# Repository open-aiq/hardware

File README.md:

# Open AIQ hardware

PCB designs (KiCad) for the Open AIQ air-quality monitor.
Firmware lives in [open-aiq/device](https://github.com/open-aiq/device); its
[`src/board.rs`](https://github.com/open-aiq/device/blob/main/src/board.rs) is the source of truth for the GPIO map.

## Layout

| Path | Contents |
| --- | --- |
| `pcb/proto2/` | Prototype 2: carrier PCB for the ESP32-S3 devkit with sensor connectors |
| `lib/` | Our own symbols and footprints, shared by every board |
| `scripts/` | `export.sh`, which builds a board's outputs from the command line |

Each PCB folder holds the KiCad project, the schematic and assembly PDFs, and
the fabrication outputs (Gerbers and BOM) under `fab/`. Its README
covers the parts, the pin map and what to check before you build.

Still to come: an SMT board with the ESP32-S3 module on it (in progress on the
`smt` branch), a battery-powered revision, and a 3D-printed enclosure.

## Working in KiCad

Everything here is a normal KiCad 10 project, and the KiCad files are the source
of truth. Open `pcb/<board>/<board>.kicad_pro` and edit the schematic and board
as you would any other design.

- **Libraries need no setup.** Our own symbols and footprints live in
  [`lib/`](lib), and each project finds them through `${KIPRJMOD}`. A part we've
  adapted, like the ESP32-S3 module with JLCPCB-sized vias, is saved there under
  its own name, so *Update footprints from library* keeps our changes.
- **Rules live in the project.** Net classes (wider power tracks), clearances and
  via sizes are set in *Board Setup*, so DRC is ready to go. The board opens
  with zero ERC and DRC messages. If you see one, it's new.
- **Outputs come from a jobset.** Open `<board>.kicad_jobset` from the project
  window (or *File → Jobsets*) and run it. It checks ERC and DRC, then writes the
  schematic PDF, the copper PDFs, Gerbers, drill files, the BOM and the
  placement file (plus a JLCPCB BOM for the SMT board).
- **The command line runs the same jobset.** From the repo root,
  `scripts/export.sh pcb/<board>` runs it with `kicad-cli`, then adds what KiCad
  doesn't make on its own: a zipped Gerber set, a JLCPCB-format placement file,
  3D renders and a printable PDF. That PDF has the
  schematic, the copper, a drill map, the board's hand assembly guide (if it
  has one), the BOM and placement tables, and the three renders. Merging it needs
  `qpdf` or Python's `pypdf`, and the script checks for one before it starts.

Please commit your KiCad edits and the regenerated outputs together, so the PDFs
and fab files always match the design.

## Roadmap

Planned work is tracked on the [Open AIQ Roadmap](https://github.com/orgs/open-aiq/projects/1) board.

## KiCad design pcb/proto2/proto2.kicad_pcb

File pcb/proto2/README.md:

# Proto2: devkit carrier

Proto2 is the board we use to get Open AIQ off the breadboard. The OLED sits
top-left with three buttons under it, the sensors take the middle, and your
ESP32-S3 devkit plugs into two sockets on the right with its antenna past the
top edge. It's single-sided (all copper on the bottom) and everything is
through-hole, with unplated holes, so a local shop can make it, you can etch
it at home, and you can solder it by hand.

| Top | Bottom |
| --- | --- |
|  |  |

## What's on it

| Ref | Part | Wiring |
| --- | --- | --- |
| J4, J5 | ESP32-S3-DevKitC-1, or a pin-compatible clone, on two 1×22 sockets 25.4 mm (1.0 in) apart: J4 takes devkit pins 1–22, J5 pins 23–44. The schematic shows the devkit itself as U1 | All signals are on the left header (J4). USB faces the bottom edge |
| J1 | PMS5003 particulate sensor, through its 4-wire cable, on a 1×4 socket | `TX RX VCC GND` from left to right, the cable's order, printed on the board. TX and RX are the sensor's, so TX goes to GPIO 17 (ESP RX) and RX to GPIO 18 (ESP TX). 5 V. SET and RESET aren't wired |
| J2 | 1.3 in SH1106 128×64 I2C OLED module, 4-pin socket | I2C, `GND VCC SCL SDA` from left to right, the order printed on the module's front. The module lies flat over the OLED box |
| J3, J6 | SHT30 breakout with 6 pins, on a 1×4 socket (J3) and a 1×2 socket (J6) 10.16 mm apart | I2C on J3, `SDA SCL GND VIN` from left to right on the silkscreen. J6 holds the 2 pins on the far edge, opposite SCL and SDA, for support only |
| SW1, SW2, SW3 | Right, left and pair buttons, 6 × 6 mm 4-leg tactile switches | GPIO 15, GPIO 6 and GPIO 7, active-low |
| R1, R2 | 4.7 kΩ I2C pull-ups | SDA (GPIO 5), SCL (GPIO 4) to 3.3 V, under the OLED module |
| C1–C4 | Bulk and decoupling capacitors | 47 µF + 100 nF on 5 V (C1, C2) and 10 µF + 100 nF on 3.3 V (C3, C4). All four lie flat under the devkit, in the middle of the space between its sockets |

The pins match [`src/board.rs`](https://github.com/open-aiq/device/blob/main/src/board.rs)
in open-aiq/device. Rev B moved several pins so every trace fits on one side of
the board, so flash firmware with the matching `board.rs` before you plug a
devkit in. Older breadboard builds used the previous map (SDA 8, SCL 9, buttons
4 and 5), which you'll find in the firmware README. A few pins are worth knowing
about:

- **SW3 Pair (GPIO 7)** starts BLE pairing with the phone app when you hold it
  for 3 s. Holding left and right together does the same.
- **The PMS5003 sleeps and wakes by UART command.** The 4-wire cable leaves
  SET and RESET unconnected, which the sensor's manual says is fine: it pulls
  them up itself, so it runs. The firmware sends the manual's sleep and wake
  commands between readings instead of driving a pin, so GPIO 8 and 16 are
  free. There's no reset command, so a sensor that hangs needs a power cycle.

Everything to print is in [`proto2.pdf`](proto2.pdf): the schematic, the
bottom copper (mirrored, as you'd see it from below), a drill map of every hole
by size, a one-page hand assembly guide, the BOM, the placement (CPL) list, and
three 3D renders (an angled view, the top and the bottom). Every page is A4.
The bottom copper is 1:1, so print it at 100% ("Actual size", not "Fit to
page") and the board outline measures 145.5 × 68 mm. You can lay your parts on
the paper to check the fit before you order. The drill map is scaled to fit.
Wondering why a part is there, or why it has that value?
[`proto2-rationale.pdf`](proto2-rationale.pdf) walks through every component and
pin choice, with references to the datasheets.

## Revisions

- **Rev I** (this one) takes the PMS5003 on a 4-wire cable (`TX RX VCC GND`)
  instead of the 8-pin adapter. J1 becomes a 1×4 socket with TX and RX
  sitting where the GPIO 17 and 18 tracks already ended, and the 5 V feed
  steps over the GND pin to reach VCC. SET and RESET aren't wired any more,
  so R3, R4, their `PMS PULL-UPS` box and the GPIO 8 and 16 tracks are gone;
  the firmware sleeps and wakes the sensor with UART commands. A new
  `No ground finger` area keeps the fill out of the old RESET track's path.
  The board also shrinks to 145.5 × 68 mm, 1.5 mm narrower and 7.5 mm
  shorter. The 3.3 V track along the bottom moves up under SDA and SCL
  (which move up about 1 mm too), keeping a 1.0 mm gap between them, so the
  bottom edge follows. The mounting holes move with the corners, and the
  bottom scene shrinks to fit the free space under J1.
  It's made one way now: single-sided with unplated holes (the plated,
  2-layer set is gone). C1–C4 move down into the middle of the space between
  the devkit sockets and lie flat, legs side by side, so they rest on the
  board instead of standing under the devkit. The `Open AIR IQ` lettering
  leaves the bottom copper to make room, and the bottom silkscreen gains a QR
  code to [docs.air-iq.net/proto2](https://docs.air-iq.net/proto2/), with a
  note inviting you to help build it.
  Flash firmware that uses the commands before you plug the sensor in.
- **Rev H** is about home etching and reading the board.
  The schematic now joins every part with real wires; only ground, 3.3 V and
  5 V use power symbols. Signal tracks widen from 1.0 to 1.2 mm and the 5 V
  feed to 2.0 mm, and tracks that run side by side keep an even gap. The
  ground fill is never narrower than 1 mm: KiCad drops anything thinner, and
  a DRC rule in `proto2.kicad_dru` flags a neck that's still carrying a
  connection. Dead-end strips of fill that reach no ground pin (the wedges
  between the button tracks, under the PMS5003 bed and between the devkit and
  J1) are cut back with `No ground finger` rule areas, with 45° corners. R1
  and R2 (I2C pull-ups) lie flat under the OLED module, and C1–C4 use the 1 cm
  of space under the devkit, right beside its 3V3 and 5V pins. The SHT30
  socket, R3 and R4 (in the `PMS PULL-UPS` box) and J1 sit in one row along
  the bottom, J1 next to the devkit, so the 5 V feed is one straight track.
  The PMS5003 bed sits 10 mm further right to leave the OLED some room, and
  the buttons sit 3 mm lower. R3 and R4 move to a 7.62 mm pitch, and J3 turns
  round (its pins now read `SDA SCL GND VIN`). The board grows to 147 × 75.5 mm to
  make room, and the bottom copper under the devkit says `Open AIR IQ`. The
  silkscreen is bold and uppercase with rounded double-line boxes, and the
  devkit's pin names are printed inside its sockets. We also gave it a friendlier
  face: the OLED box smiles and says hello, and the bottom has a little scene
  with our monitor waving from the hills and a thank-you note. The pin map
  matches rev G.
- **Rev G** widens the gap around the ground fill from 0.8 to
  0.9 mm, so there's more room between ground and every other track. To keep
  the SHT30's ground pin on the fill, the 3.3 V track to R4 moved 0.4 mm
  right. Nothing else moved, and the pin map and parts match rev F.
- **Rev F** adds four M2 holes so you can screw the PMS5003 to
  the board, on the sensor's own 45 × 33 mm hole pattern. It also fixes the
  SHT30 socket: the 2-pin row now sits opposite SCL and SDA, 10.16 mm from
  the 4-pin row, which is where the pins are on a real breakout (rev E had it
  6.35 mm away, opposite GND and SCL). Signal tracks widen again, from 0.8 to
  1.0 mm, with the I²C pair re-spaced to fit, and SDA now runs straight into
  the OLED socket instead of looping over it. Two tracks moved to stay clear
  of the screw heads. The pin map and the other parts match rev E.
- **Rev E** swaps the tiny 1.25 mm PMS5003 connector for a 1×8,
  2.54 mm socket that takes the sensor's adapter board, with a clear area
  around it so the adapter can lie flat. Every track is wider and further
  apart: signals 0.8 mm, power 1.5 mm, at least 0.4 mm between them, and
  0.8 mm around the ground fill. There are no narrow spots left, and ground
  comes entirely from the fill. To make room, R3, R4, C1–C4 moved, R1 and R2
  use a 7.62 mm pitch, and the OLED socket and its area sit 2.5 mm lower.
  The pin map is the same as rev D.
- **Rev D** widens the copper wherever there's room. Signal tracks
  go from 0.3 to 0.5 mm (0.4 or 0.3 mm where they squeeze between header
  pins), most power and ground tracks from 0.8 to 1.0 mm, and the ground fill
  keeps 0.5 mm from everything else, up from 0.3 mm. That makes it kinder to
  hand soldering and home etching. Nothing moved, so the parts, pins and
  silkscreen match rev C apart from the rev label.
- **Rev C** rotates the OLED socket so it reads `GND VCC SCL SDA`,
  the order printed on the module. Rev B had it mirrored, which would have
  swapped 3.3 V and ground. It also widens the ground tracks where there's
  room and changes C1 from 100 µF to 47 µF. The pin map is the same as rev B.
- **Rev B** made the board single-sided, added the pair button and moved to
  today's pin map.
- **Rev A** was the first, two-layer carrier.

## Before you build

- **Check your OLED's pin order.** The socket reads `GND VCC SCL SDA` from left
  to right, and the silkscreen says so too. Hold your module face-up with its
  pins along the top: its labels should read the same. Some modules swap GND
  and VCC, and plugging one in backwards can damage it.
- **Clone devkits need the 5 V pad bridged.** Many DevKitC-1 clones have an
  `IN-OUT` solder jumper next to the 5V pin. Until you bridge it, USB power
  doesn't reach that pin, and the PMS5003 stays dark. Once it's bridged, don't
  feed 5 V into the pin while USB is plugged in.
- **C1–C4 sit under the devkit.** There's about 1 cm between the board and
  the devkit, so pick capacitors no taller than 8 mm (see [Parts](#parts)),
  and plug the devkit in once to check it seats fully before you solder them.
- **The OLED lies flat over its box.** It plugs into J2 face-up and
  rests over that area, so the only parts under it are R1 and R2, lying flat.
  Solder those before you fit the screen. If your module sits lower than the
  socket's usual 8.5 mm, check they clear it.
- **Check your SHT30 against the socket.** The 2-pin row sits 10.16 mm
  (4 breadboard holes) from the 4-pin row, opposite SCL and SDA, as measured on
  our breakout. If yours differs, the 4-pin row still works, and you can leave
  the 1×2 socket out.
- **The PMS5003 plugs in through its 4-wire cable.** Its 2.54 mm end goes
  into J1, reading `TX RX VCC GND` from left to right like the silkscreen. If
  your cable ends in a small adapter board, it can lie flat over the dashed
  area around J1. If your cable ends in female pins instead, fit a 1×4 male
  header in J1's holes; the footprint is the same.
- **The PMS5003 sits on the marked bed.** Fix it with four M2 self-tapping
  screws from below, through the holes in the bed's corners and into the
  sensor's case, or stick it down with double-sided foam tape. Keep the vents
  facing the top edge so it doesn't pull in warm air from the devkit. The
  bottom copper stays clear around each hole, so a screw head can't touch a
  track. Its case is metal, but there's no copper on top, so it can't short
  anything.
- **The capacitors lie flat.** C1–C4 sit between the devkit sockets with
  their legs side by side. Push the legs through, then fold the body down
  over the outline beside its pads, so the devkit clears it. On C1 and C3 the
  long leg goes in the square pad by the `+`, and the can's stripe sits over
  the striped side of the outline.
- **The QR code on the bottom** opens
  [docs.air-iq.net/proto2](https://docs.air-iq.net/proto2/), with what the
  board does, its revisions and how to help. It's silkscreen, so a board you
  etch yourself won't have it.
- **The devkit's antenna hangs off the top edge.** That's on purpose: copper
  under an antenna weakens WiFi and BLE, so the ground fill also stops short of
  that end. Its USB end sits about 7 mm in from the bottom edge, with nothing
  tall underneath, so a USB plug still fits.
- **R8 modules use GPIO 35, 36 and 37 for PSRAM.** Proto2 leaves them
  unconnected, so keep it that way if you add anything.
- **The status LED is on the devkit.** The firmware drives both GPIO 48
  (DevKitC-1 v1.0) and GPIO 38 (v1.1), so it lights on either. Proto2 leaves
  both pins free.

## First power-up

A few quick checks before you trust the readings:

1. **Check the PMS5003 cable with a multimeter first.** Pin 1 on the sensor
   (VCC) should reach the cable pin that sits in J1's `VCC`, and pin 2 (GND)
   J1's `GND`. Some cables come wired in reverse. That won't damage anything, but the
   sensor stays silent.
2. **Measure 5 V at J1's `VCC` (pin 3) with the fan running.** The PMS5003 needs at least
   4.5 V. A long or thin USB cable, plus the devkit's own power path, can pull
   the 5V pin below what your charger supplies.
3. **Read the serial log.** The I2C scan at boot should find `0x3C` (OLED) and
   `0x44` (SHT30).
4. **Look at the screen.** It should read upright with the pins at the top. If it
   shows upside down, the firmware's display setup notes how to flip it.

## Parts

You'll find the generated list in [`fab/proto2-bom.csv`](fab/proto2-bom.csv).
Every part has a manufacturer part number and an LCSC number, so you can buy
them from LCSC, Mouser or DigiKey, or have a board house fit them. Any part with
the same size, pitch and height works too.

| Qty | Part | Manufacturer part | LCSC | Notes |
| --- | --- | --- | --- | --- |
| 2 | 1×22 female header, 2.54 mm, 8.5 mm tall | Megastar ZX-PM2.54-1-22PY | C7499337 | Sockets for the devkit (J4, J5) |
| 3 | 1×4 female header, 2.54 mm, 8.5 mm tall | Megastar ZX-PM2.54-1-4PY | C7499324 | OLED (J2), SHT30 (J3) and the PMS5003 cable (J1) |
| 1 | 1×2 female header, 2.54 mm, 8.5 mm tall | Megastar ZX-PM2.54-1-2PY | C7499322 | SHT30's far-edge pins (J6) |
| 3 | 6 × 6 mm through-hole tactile switch, 4-leg, 4.3 mm tall | Omron B3F-1000 | C93157 | SW1, SW2, SW3 |
| 2 | 4.7 kΩ ±1% metal film resistor, 1/4 W axial | YAGEO MFR-25FTE52-4K7 | C173023 | R1, R2. These sit on a 7.62 mm pitch, so bend the legs close to the body |
| 1 | 47 µF 25 V electrolytic, 6.3 mm radial, 2.5 mm pitch, 5 mm tall | CX KF476M025E05RR0VH2FP0 | C45704 | C1. It lies flat under the devkit, so keep it 6.3 mm across at most |
| 1 | 10 µF 50 V electrolytic, 5 mm radial, 2 mm pitch, 7 mm tall | CX KS106M050D07RR0VH2FP0 | C45669 | C3, also lying flat under the devkit |
| 2 | 100 nF 50 V X7R ceramic, 5 mm pitch | Murata RDER71H104K0M1H03A | C527620 | C2, C4, also lying flat under the devkit |
| 4 | M2 self-tapping screw, pan head, about 5 mm long | | | Optional, to hold the PMS5003 (H5). Use one short enough not to reach inside the sensor |

The devkit, PMS5003 (with its 4-wire cable), SHT30 breakout and OLED
module aren't on the list: you buy them separately and plug them in.

## Ordering

[`fab/proto2-gerbers.zip`](fab/proto2-gerbers.zip) holds the Gerbers and the
drill file: bottom copper, bottom solder mask, top and bottom silkscreen, the
outline, and every hole in one unplated drill file. Upload it to a local shop,
JLCPCB or PCBWay as it is, and order it as a 1-layer board. If you're etching
or milling it yourself, the bottom copper page in `proto2.pdf` and the drill
file are all you need; you'll go without the silkscreen and the QR code.

Unplated pads are held only by their glue to the board, so they lift more
easily than plated ones. Heat each joint briefly, and try not to resolder a
pad more than you need to.

We haven't placed an order yet, so treat these settings as our first guess:

| Setting | Value |
| --- | --- |
| Size | 145.5 × 68 mm |
| Layers | 1 (bottom copper only), holes unplated |
| Thickness | 1.6 mm |
| Min track / clearance | 1.2 / 0.4 mm (power 1.5 mm, the 5 V feed 2.0 mm), with 0.9 mm around the ground fill, which is never narrower than 1 mm |
| Min hole | 0.8 mm (resistor and capacitor leads), plus four 2.2 mm holes for the PMS5003 screws; no vias |
| Surface finish | HASL is fine |

Every part is through-hole, so you can solder it yourself; the hand assembly
guide in the PDF walks you through it. To buy the parts, the BOMs carry their
LCSC and manufacturer part numbers:
[`fab/proto2-jlc-bom.csv`](fab/proto2-jlc-bom.csv) (by LCSC number) and
[`fab/proto2-pcbway-bom.csv`](fab/proto2-pcbway-bom.csv) (by manufacturer part
number). [`fab/proto2-jlc-cpl.csv`](fab/proto2-jlc-cpl.csv) is the placement
file, if a board house offers through-hole assembly on a 1-layer board; we
haven't tried that, so check with them first. If a part runs out, pick
another with the same size, pitch and height.

## Editing

Open `proto2.kicad_pro` in KiCad 10. The repo's [Working in KiCad](../../README.md#working-in-kicad)
guide covers libraries, rules and outputs. These are ours, in [`lib/`](../../lib):

- the devkit, SHT30 and PMS5003 cable socket footprints, and the PMS5003
  mounting holes (a board-only footprint with a copper keep-out for each
  screw head). Each socket row is its own footprint, so every reference is one
  part a board house can fit: the devkit's left and right rows (J4, J5) and the
  SHT30's 1×4 and 1×2 (J3, J6). The devkit sockets mark the devkit's GND pins
  and its two 3V3 pins as joined inside the devkit (KiCad *jumper pad
  groups*), so they don't need tracks between them
- the LCSC, Manufacturer and MPN fields on every part, which
  `scripts/export.sh` turns into the JLCPCB and PCBWay BOMs
- the lying-down capacitor footprints for C1–C4, adapted from KiCad's radial
  and disc ones, with the body drawn beside the pads and the 3D model laid flat
- the arrow and phone-with-Bluetooth icons under the buttons, which are
  board-only footprints you can move
- the sensor symbols

To refresh the outputs, run `proto2.kicad_jobset` in KiCad, or this from the repo
root:

```sh
scripts/export.sh pcb/proto2
```

Both stop if ERC or DRC finds a problem. The home-etching rules (1.2 mm
signals, 1.5 mm power, no ground neck under 1 mm) live in
[`proto2.kicad_dru`](proto2.kicad_dru), next to the board.

The hand assembly guide is `proto2-guide.typ`; `scripts/export.sh` builds it
into the PDF, so update it if you change a part.

The design rationale is written in [Typst](https://typst.app). If you change a
part, update `proto2-rationale.typ` too, then rebuild the PDF from this folder:

```sh
typst compile proto2-rationale.typ
```

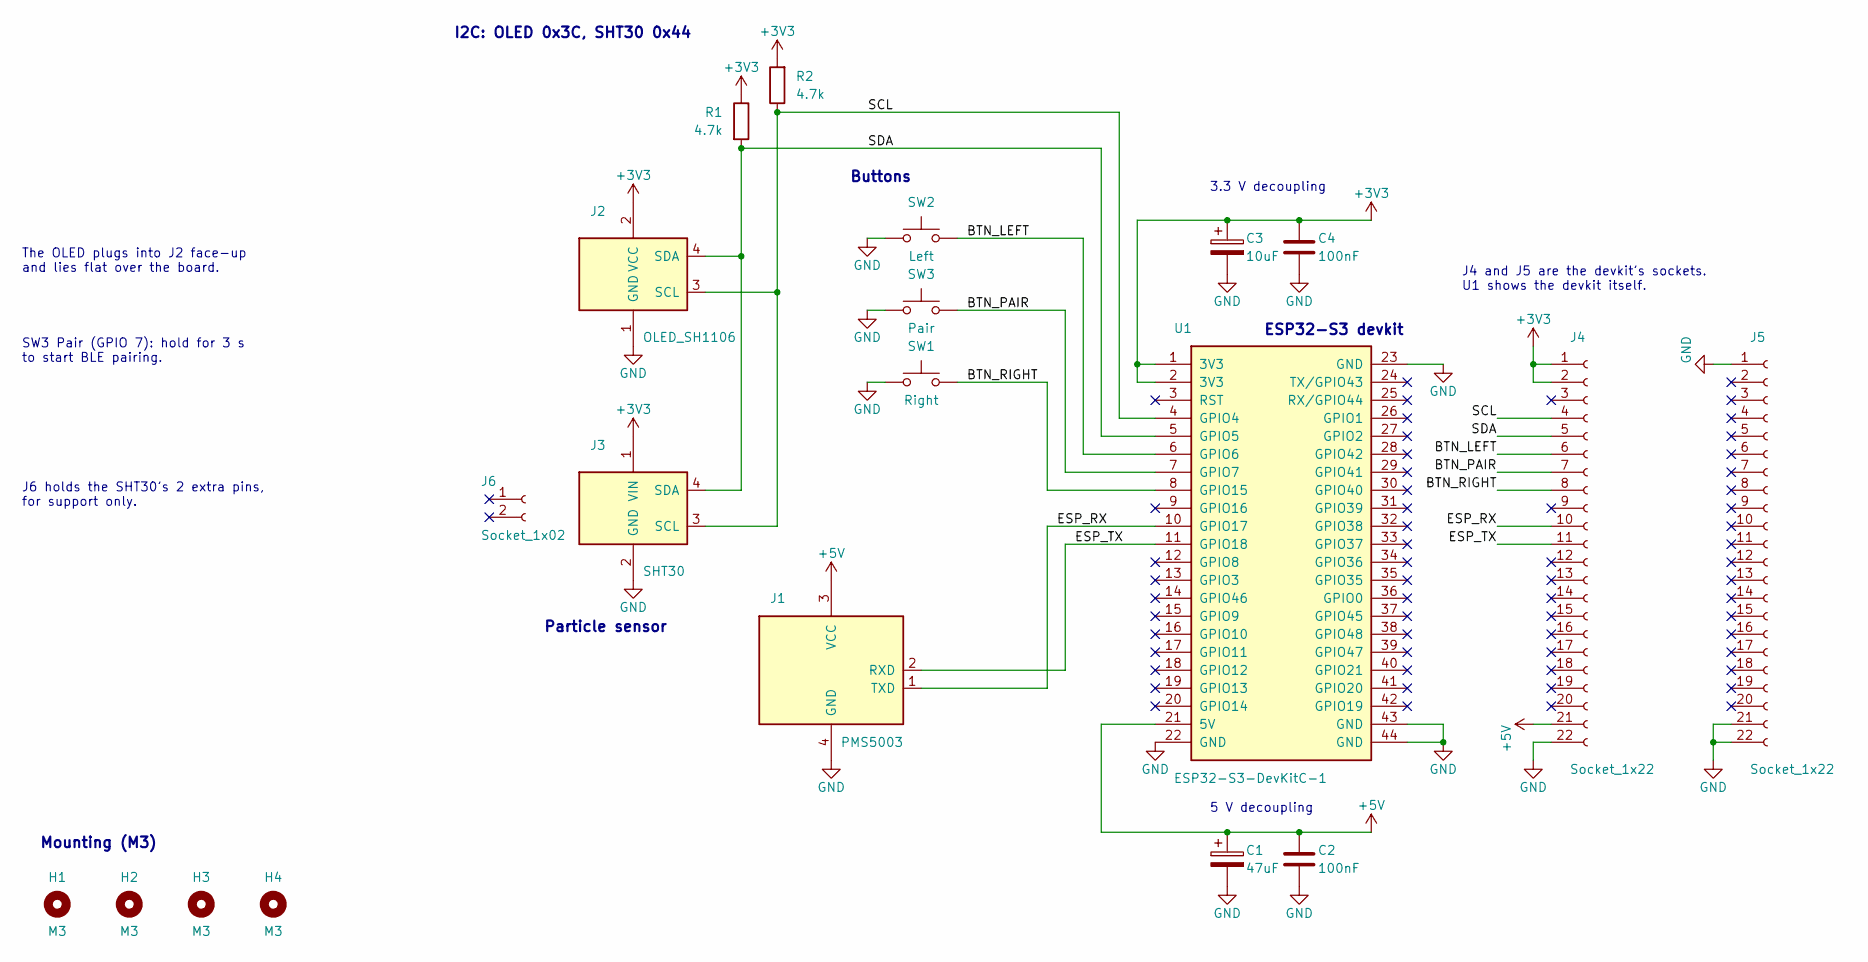
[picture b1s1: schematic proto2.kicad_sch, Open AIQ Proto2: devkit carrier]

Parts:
C1: 47uF; CP_Radial_D6.3mm_L5.0mm_P2.50mm_Lying; Part 47 µF 25 V electrolytic, 6.3 × 5 mm rad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; LCSC C45704
C2, C4: 100nF; C_Disc_D5.0mm_W2.5mm_P5.00mm_Lying; Part 100 nF 50 V X7R ceramic, 5 mm pitch; LCSC C527620
C3: 10uF; CP_Radial_D5.0mm_L7.0mm_P2.00mm_Lying; Part 10 µF 50 V electrolytic, 5 × 7 mm radia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; LCSC C45669
H1, H2, H3, H4: M3; MountingHole_3.2mm_M3; Part M3 mounting hole
J1: PMS5003; PMS5003_Cable_Socket_1x04; Part 1×4 female header, 2.54 mm, 8.5 mm tall; LCSC C7499324
J2: OLED_SH1106; PinSocket_1x04_P2.54mm_Vertical; Part 1×4 female header, 2.54 mm, 8.5 mm tall; LCSC C7499324
J3: SHT30; SHT30_Module_Socket_1x04; Part 1×4 female header, 2.54 mm, 8.5 mm tall; LCSC C7499324
J4: Socket_1x22; ESP32-S3-DevKitC-1_Socket_Left; Part 1×22 female header, 2.54 mm, 8.5 mm tall; LCSC C7499337
J5: Socket_1x22; ESP32-S3-DevKitC-1_Socket_Right; Part 1×22 female header, 2.54 mm, 8.5 mm tall; LCSC C7499337
J6: Socket_1x02; SHT30_Module_Socket_1x02; Part 1×2 female header, 2.54 mm, 8.5 mm tall; LCSC C7499322
R1, R2: 4.7k; R_Axial_DIN0207_L6.3mm_D2.5mm_P7.62mm_Horizontal; Part 4.7 kΩ ±1% metal film resistor, 1/4 W a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; LCSC C173023
SW1: Right; SW_PUSH_6mm; Part 6 × 6 mm THT tactile switch, 4.3 mm tall; LCSC C93157
SW2: Left; SW_PUSH_6mm; Part 6 × 6 mm THT tactile switch, 4.3 mm tall; LCSC C93157
SW3: Pair; SW_PUSH_6mm; Part 6 × 6 mm THT tactile switch, 4.3 mm tall; LCSC C93157
U1: ESP32-S3-DevKitC-1; Part ESP32-S3-DevKitC-1, bought separately; 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

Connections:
+3V3: C3.1, C4.1, J2.2 (VCC), J3.1 (VIN), J4.1, J4.2, R1.1, R2.2, U1.1 (3V3), U1.2 (3V3)
+5V: C1.1, C2.1, J1.3 (VCC), J4.21, U1.21 (5V)
/BTN_LEFT: J4.6, SW2.1, U1.6 (GPIO6)
/BTN_PAIR: J4.7, SW3.1, U1.7 (GPIO7)
/BTN_RIGHT: J4.8, SW1.1, U1.8 (GPIO15)
/ESP_RX: J1.1 (TXD), J4.10, U1.10 (GPIO17)
/ESP_TX: J1.2 (RXD), J4.11, U1.11 (GPIO18)
/SCL: J2.3 (SCL), J3.3 (SCL), J4.4, R2.1, U1.4 (GPIO4)
/SDA: J2.4 (SDA), J3.4 (SDA), J4.5, R1.2, U1.5 (GPIO5)
GND: C1.2, C2.2, C3.2, C4.2, J1.4 (GND), J2.1 (GND), J3.2 (GND), J4.22, J5.1, J5.21, J5.22, SW1.2, SW2.2, SW3.2, U1.22 (GND), U1.23 (GND), U1.43 (GND), U1.44 (GND)

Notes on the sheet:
SW3 Pair (GPIO 7): hold for 3 s to start BLE pairing.
J6 holds the SHT30's 2 extra pins, for support only.
5 V decoupling
Particle sensor
The OLED plugs into J2 face-up and lies flat over the board.
ESP32-S3 devkit
I2C: OLED 0x3C, SHT30 0x44
Buttons
Mounting (M3)
3.3 V decoupling
J4 and J5 are the devkit's sockets. U1 shows the devkit itself.

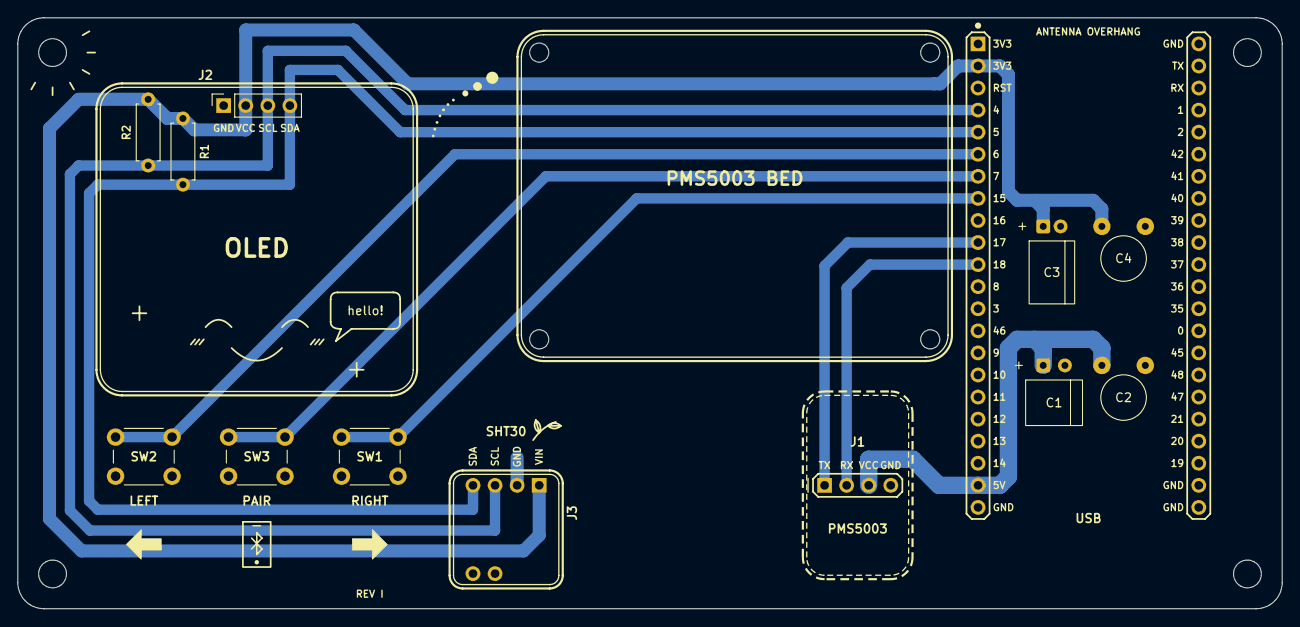
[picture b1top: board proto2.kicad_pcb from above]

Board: 2 copper layers, 145.5 x 68.0 mm, 23 parts (0 on the bottom side), 10 nets.

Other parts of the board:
G_SW1: Icon_Arrow_Right
G_SW2: Icon_Arrow_Left
G_SW3: Icon_Phone_Bluetooth
H5: PMS5003_Mount_M2

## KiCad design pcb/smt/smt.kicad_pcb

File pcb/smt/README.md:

# SMT board (rev A)

This is the first Open AIQ board with the ESP32-S3 on it, instead of on a devkit.
It does everything Proto2 does in a 56 × 44 mm board that JLCPCB can assemble
for you. You plug in the PMS5003's own cable and the OLED's Qwiic lead, and power
it from one USB-C port.

| Top | Bottom |
| --- | --- |
|  |  |

> **Status: designed, not yet ordered.** ERC and DRC pass with no errors, but no board
> has been built yet. Please read [Check before ordering](#check-before-ordering).

## What's on it

| Ref | Part | LCSC | Why |
| --- | --- | --- | --- |
| U3 | ESP32-S3-WROOM-1-N16R8 | C2913202 | Same module as the devkit: 16 MB flash, 8 MB PSRAM |
| J1 | USB-C receptacle, HRO TYPE-C-31-M-12 | C165948 | Power plus the S3's built-in USB Serial/JTAG for flashing, logs and debugging |
| U1 | USBLC6-2SC6 | C7519 | ESD protection on the USB data lines |
| F1 | 1.1 A resettable fuse (1206) | C7542963 | Protects your laptop's port if something shorts |
| U2 | AMS1117-3.3 | C6186 | 5 V to 3.3 V |
| J2 | 1.25 mm 8-pin side-entry connector | C2681529 | The PMS5003 cable from the box plugs in here |
| J3 | JST SH 4-pin (Qwiic), SM04B-SRSS-TB | C160404 | OLED on a cable: `GND 3V3 SDA SCL` |
| U4 | SHT30-DIS-B | C77361 | Temperature and humidity, on its own slotted corner |
| D1 | WS2812B-2020 | C965555 | Status LED on GPIO 48, like the devkit |
| SW1–SW4 | TS-1187A tactile switches | C318884 | RESET, BOOT, LEFT, RIGHT |

The full list is in [`fab/smt-jlc-bom.csv`](fab/smt-jlc-bom.csv). The schematic is in
[`smt.pdf`](smt.pdf), and [`smt-assembly.pdf`](smt-assembly.pdf) shows where each part goes.

### Pins

The pins match [`src/board.rs`](https://github.com/open-aiq/device/blob/main/src/board.rs)
and Proto2. SET, RESET and the LED are new, and the firmware doesn't use them yet:

| Signal | GPIO |
| --- | --- |
| I2C SDA / SCL (OLED, SHT30) | 8 / 9 |
| PMS5003 TX / RX (ESP side) | 17 / 18 |
| PMS5003 SET / RESET | 16 / 15 |
| Buttons RIGHT / LEFT | 4 / 5 |
| Status LED | 48 |
| USB D- / D+ | 19 / 20 |
| BOOT | 0 |

## Things worth knowing

- **One USB-C port does everything.** The ESP32-S3 has USB built in, so there's
  no USB-to-serial chip. Flashing, the serial console and JTAG debugging all go
  over the same cable. The firmware needs its console on USB Serial/JTAG
  (`CONFIG_ESP_CONSOLE_USB_SERIAL_JTAG`) for logs to show up.
- **The antenna hangs off the top edge.** That's on purpose: copper under the
  antenna weakens WiFi and BLE, so keep the enclosure's walls clear of it too.
- **The SHT30 sits behind a slot.** The cut-out keeps heat from the module and
  the regulator away from the sensor, so the temperature reading stays honest.
- **SET and RESET have pull-ups.** The PMS5003 keeps running if the firmware
  ignores them, and the firmware can use SET later to rest the sensor between
  readings.

## Check before ordering

We haven't built this board yet. These are the spots most likely to need a fix,
so give them a look before you place an order:

1. **PMS5003 connector fit.** C2681529 is a generic 1.25 mm side-entry header, and
   we used KiCad's Molex PicoBlade 53261 footprint for it. Compare the LCSC
   drawing with the footprint, and try the sensor's cable in a sample connector
   if you can.
2. **Part rotations in JLCPCB's preview.** KiCad and JLCPCB sometimes disagree on
   zero rotation, especially for the module, USB-C, the LED and the SOT-223
   regulator. Fix any that look turned in the assembly preview.
3. **The WS2812B runs at 3.3 V.** That keeps the data signal in spec without a
   level shifter, and it's common practice, but the LED is rated from 3.5 V.
   If it misbehaves, the fix is a 5 V supply plus a level shifter.
4. **Stock.** LCSC numbers were checked on 2026-11-08. Re-check stock when you order.

## Making it

Upload [`fab/smt-gerbers.zip`](fab/smt-gerbers.zip) to JLCPCB, turn on assembly
(top side), then add [`fab/smt-jlc-bom.csv`](fab/smt-jlc-bom.csv) and
[`fab/smt-jlc-cpl.csv`](fab/smt-jlc-cpl.csv).

| Setting | Value |
| --- | --- |
| Size | 56 × 44 mm |
| Layers | 2 |
| Thickness | 1.6 mm |
| Min track / clearance | 0.2 / 0.15 mm (power 0.4 mm) |
| Vias | 0.6 mm pad, 0.3 mm drill |
| Assembly | Top side, all parts |

## Editing

Open `smt.kicad_pro` in KiCad 10. The repo's [Working in KiCad](../../README.md#working-in-kicad)
guide covers libraries, rules and outputs. A few things specific to this board:

- **Two footprints are our own copies.** They live in [`lib/`](../../lib):
  `ESP32-S3-WROOM-1_JLC` has 0.3 mm thermal vias, and
  `USB_C_Receptacle_HRO_TYPE-C-31-M-12_BoardEdge` has its silkscreen trimmed at
  the board edge. Edit them there, not on the board.
- **The SHT30 slot has keep-out zones.** They're the rule areas along the slot on
  both copper layers, and they stop traces from crowding the cut-out. If you
  move the slot, move them too.
- **Some reference designators only show on the assembly drawing.** Five small
  parts (C5, C6, R3, R5, R6) had no room for silkscreen labels. They're
  labelled in [`smt-assembly.pdf`](smt-assembly.pdf), along with every other part.
- **The traces came from an autorouter.** Feel free to clean them up by hand.
  Keep the USB D+/D- pair short and side by side, and keep copper away from the
  antenna edge.

To refresh the outputs, run the jobset in KiCad, or this from the repo root:

```sh
RENDER_ZOOM=1.15 scripts/export.sh pcb/smt
```

The board was first laid out by scripts. They're in this repo's history (commit
`fc827ce`, `pcb/smt/tools/`), but the KiCad files have moved on since, so don't
re-run them.

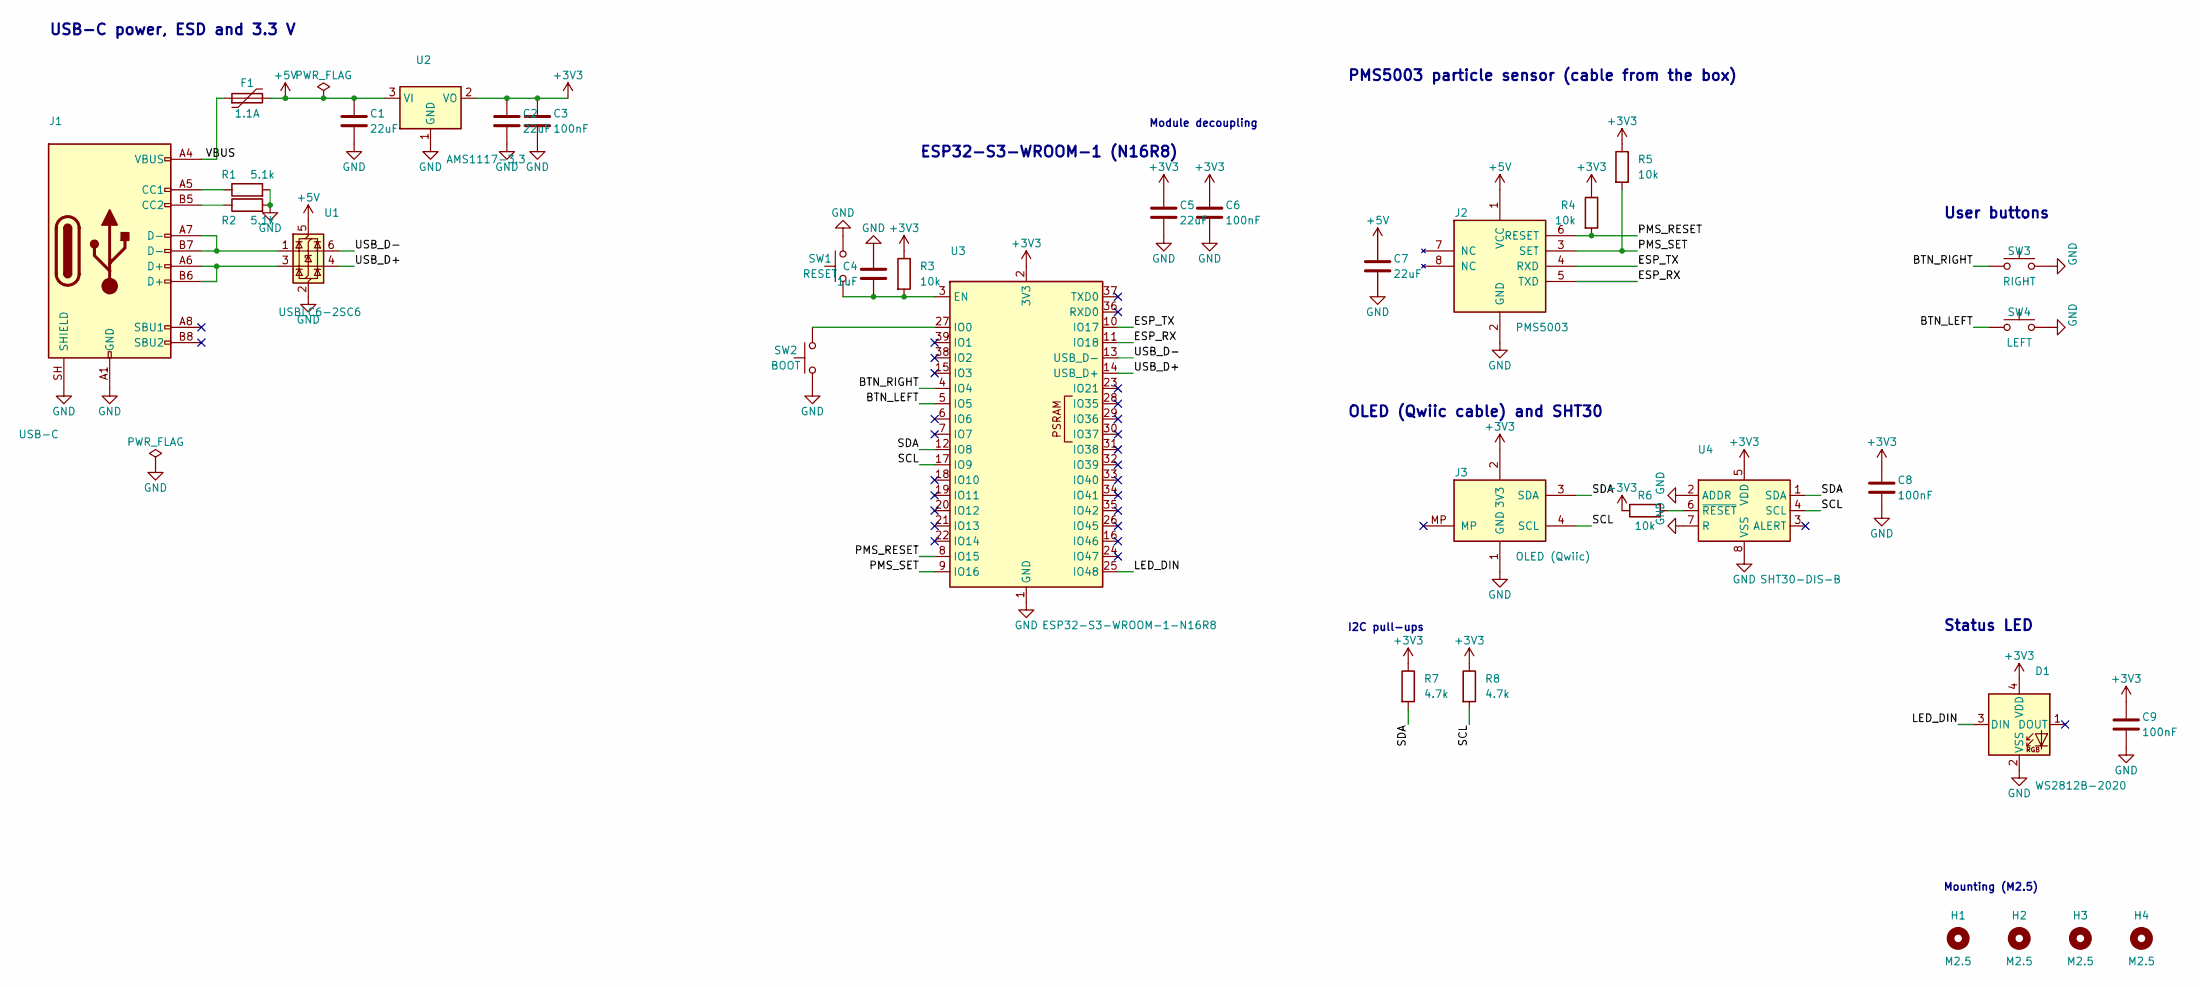
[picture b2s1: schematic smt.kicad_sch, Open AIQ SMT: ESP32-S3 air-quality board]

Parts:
C1, C2, C5, C7: 22uF; C_0805_2012Metric; LCSC C45783
C3, C6, C8, C9: 100nF; C_0603_1608Metric; LCSC C14663
C4: 1uF; C_0603_1608Metric; LCSC C15849
D1: WS2812B-2020; LED_WS2812B-2020_PLCC4_2.0x2.0mm; LCSC C965555
F1: 1.1A; Fuse_1206_3216Metric; LCSC C7542963
H1, H2, H3, H4: M2.5; MountingHole_2.7mm_M2.5
J1: USB-C; USB_C_Receptacle_HRO_TYPE-C-31-M-12_BoardEdge; LCSC C165948
J2: PMS5003; Molex_PicoBlade_53261-0871_1x08-1MP_P1.25mm_Horizontal; LCSC C2681529
J3: OLED (Qwiic); JST_SH_SM04B-SRSS-TB_1x04-1MP_P1.00mm_Horizontal; LCSC C160404
R1, R2: 5.1k; R_0603_1608Metric; LCSC C23186
R3, R4, R5, R6: 10k; R_0603_1608Metric; LCSC C25804
R7, R8: 4.7k; R_0603_1608Metric; LCSC C23162
SW1: RESET; SW_Push_1P1T_XKB_TS-1187A; LCSC C318884
SW2: BOOT; SW_Push_1P1T_XKB_TS-1187A; LCSC C318884
SW3: RIGHT; SW_Push_1P1T_XKB_TS-1187A; LCSC C318884
SW4: LEFT; SW_Push_1P1T_XKB_TS-1187A; LCSC C318884
U1: USBLC6-2SC6; SOT-23-6; LCSC C7519
U2: AMS1117-3.3; SOT-223-3_TabPin2; LCSC C6186
U3: ESP32-S3-WROOM-1-N16R8; ESP32-S3-WROOM-1_JLC; LCSC C2913202
U4: SHT30-DIS-B; Sensirion_DFN-8-1EP_2.5x2.5mm_P0.5mm_EP1.1x1.7mm; LCSC C77361

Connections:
+3V3: C2.1, C3.1, C5.1, C6.1, C8.1, C9.1, D1.4 (VDD), J3.2 (3V3), R3.1, R4.1, R5.1, R6.1, R7.1, R8.1, U2.2 (VO), U3.2 (3V3), U4.5 (VDD)
+5V: C1.1, C7.1, F1.2, J2.1 (VCC), U1.5 (VBUS), U2.3 (VI)
/BTN_LEFT: SW4.1, U3.5 (IO5)
/BTN_RIGHT: SW3.1, U3.4 (IO4)
/ESP_RX: J2.5 (TXD), U3.11 (IO18)
/ESP_TX: J2.4 (RXD), U3.10 (IO17)
/LED_DIN: D1.3 (DIN), U3.25 (IO48)
/PMS_RESET: J2.6 (RESET), R4.2, U3.8 (IO15)
/PMS_SET: J2.3 (SET), R5.2, U3.9 (IO16)
/SCL: J3.4 (SCL), R8.2, U3.17 (IO9), U4.4 (SCL)
/SDA: J3.3 (SDA), R7.2, U3.12 (IO8), U4.1 (SDA)
/USB_D+: U1.4 (I/O2), U3.14 (USB_D+)
/USB_D-: U1.6 (I/O1), U3.13 (USB_D-)
/VBUS: F1.1, J1.A4 (VBUS), J1.A9 (VBUS), J1.B4 (VBUS), J1.B9 (VBUS)
GND: C1.2, C2.2, C3.2, C4.1, C5.2, C6.2, C7.2, C8.2, C9.2, D1.2 (VSS), J1.A1 (GND), J1.A12 (GND), J1.B1 (GND), J1.B12 (GND), J1.SH (SHIELD), J2.2 (GND), J3.1 (GND), R1.2, R2.2, SW1.2, SW2.1, SW3.2, SW4.2, U1.2 (GND), U2.1 (GND), U3.1 (GND), U3.40 (GND), U3.41 (GND), U4.2 (ADDR), U4.7 (R), U4.8 (VSS), U4.9 (VSS)
unnamed: J1.A5 (CC1), R1.1
unnamed: J1.B5 (CC2), R2.1
unnamed: J1.A6 (D+), J1.B6 (D+), U1.3 (I/O2)
unnamed: J1.A7 (D-), J1.B7 (D-), U1.1 (I/O1)
unnamed: C4.2, R3.2, SW1.1, U3.3 (EN)
unnamed: SW2.2, U3.27 (IO0)
unnamed: R6.2, U4.6 (~RESET)

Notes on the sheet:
USB-C power, ESD and 3.3 V
PMS5003 particle sensor (cable from the box)
Module decoupling
Status LED
I2C pull-ups
Mounting (M2.5)
User buttons
OLED (Qwiic cable) and SHT30
ESP32-S3-WROOM-1 (N16R8)

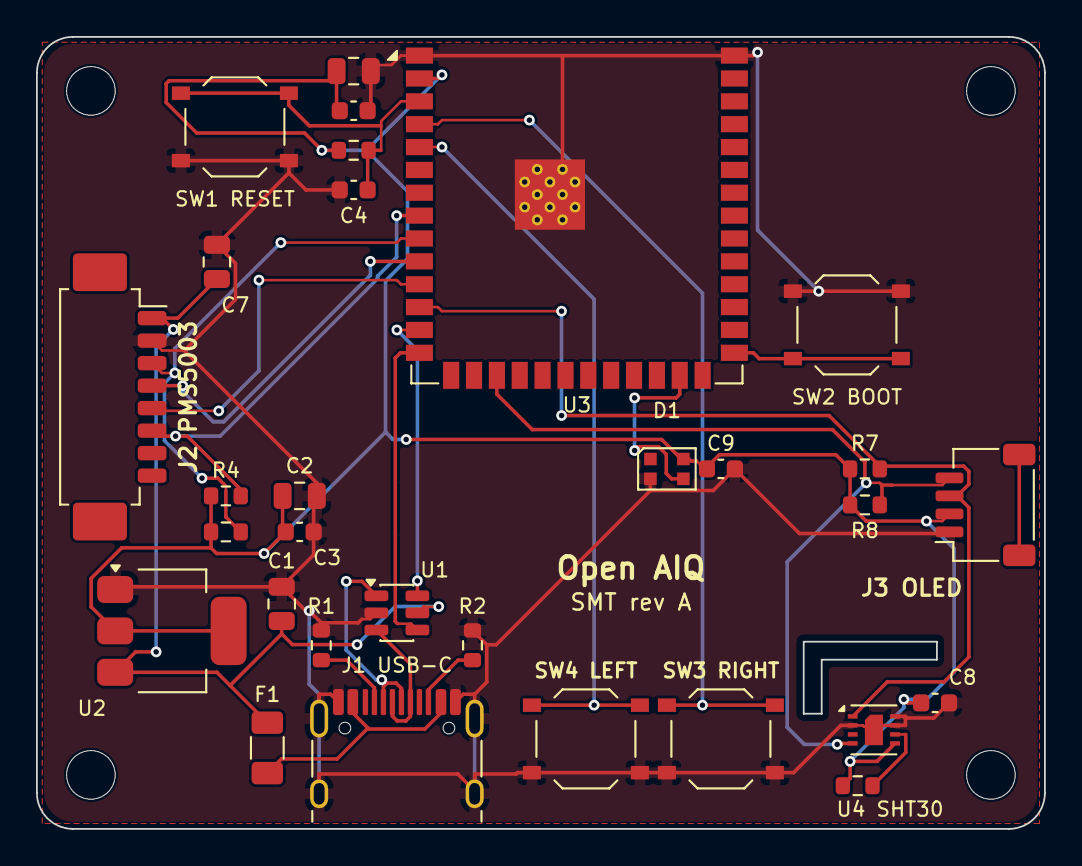
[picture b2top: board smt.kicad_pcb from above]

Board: 2 copper layers, 56.0 x 44.0 mm, 34 parts (0 on the bottom side), 22 nets.

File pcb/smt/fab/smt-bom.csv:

"Reference","Value","Footprint","Qty","LCSC","Datasheet"
"C1,C2,C5,C7","22uF","Capacitor_SMD:C_0805_2012Metric","4","C45783",""
"C3,C6,C8,C9","100nF","Capacitor_SMD:C_0603_1608Metric","4","C14663",""
"C4","1uF","Capacitor_SMD:C_0603_1608Metric","1","C15849",""
"D1","WS2812B-2020","LED_SMD:LED_WS2812B-2020_PLCC4_2.0x2.0mm","1","C965555",""
"F1","1.1A","Fuse:Fuse_1206_3216Metric","1","C7542963",""
"J1","USB-C","Connector_USB:USB_C_Receptacle_HRO_TYPE-C-31-M-12","1","C165948",""
"J2","PMS5003","Connector_Molex:Molex_PicoBlade_53261-0871_1x08-1MP_P1.25mm_Horizontal","1","C2681529",""
"J3","OLED (Qwiic)","Connector_JST:JST_SH_SM04B-SRSS-TB_1x04-1MP_P1.00mm_Horizontal","1","C160404",""
"R1,R2","5.1k","Resistor_SMD:R_0603_1608Metric","2","C23186",""
"R3-R6","10k","Resistor_SMD:R_0603_1608Metric","4","C25804",""
"R7,R8","4.7k","Resistor_SMD:R_0603_1608Metric","2","C23162",""
"SW1","RESET","Button_Switch_SMD:SW_Push_1P1T_XKB_TS-1187A","1","C318884",""
"SW2","BOOT","Button_Switch_SMD:SW_Push_1P1T_XKB_TS-1187A","1","C318884",""
"SW3","RIGHT","Button_Switch_SMD:SW_Push_1P1T_XKB_TS-1187A","1","C318884",""
"SW4","LEFT","Button_Switch_SMD:SW_Push_1P1T_XKB_TS-1187A","1","C318884",""
"U1","USBLC6-2SC6","Package_TO_SOT_SMD:SOT-23-6","1","C7519",""
"U2","AMS1117-3.3","Package_TO_SOT_SMD:SOT-223-3_TabPin2","1","C6186",""
"U3","ESP32-S3-WROOM-1-N16R8","RF_Module:ESP32-S3-WROOM-1","1","C2913202","https://www.espressif.com/sites/default/files/documentation/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"
"U4","SHT30-DIS-B","Sensor_Humidity:Sensirion_DFN-8-1EP_2.5x2.5mm_P0.5mm_EP1.1x1.7mm","1","C77361",""

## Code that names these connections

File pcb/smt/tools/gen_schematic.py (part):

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     lcsc="C2681529", refpos=(261.62, 64.77, "left"), valpos=(271.78, 83.82, "left"))
pwr("+5V", PX, 60.96); pwr("GND", PX, 86.36)
PR = PX + 12.7
wire((PR, 68.58), (284.48, 68.58), (292.1, 68.58)); junc(284.48, 68.58); label("PMS_RESET", 292.1, 68.58)
wire((PR, 71.12), (289.56, 71.12), (292.1, 71.12)); junc(289.56, 71.12); label("PMS_SET", 292.1, 71.12)
wire((PR, 73.66), (292.1, 73.66)); label("ESP_TX", 292.1, 73.66)
wire((PR, 76.2), (292.1, 76.2)); label("ESP_RX", 292.1, 76.2)
R("R4", "10k", 284.48, 64.77, refpos=(281.94, 63.5, "right"), valpos=(281.94, 66.04, "right")); pwr("+3V3", 284.48, 60.96)
R("R5", "10k", 289.56, 57.15); pwr("+3V3", 289.56, 53.34)
wire((289.56, 60.96), (289.56, 71.12))       # R5 lead crosses PMS_RESET without connecting
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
